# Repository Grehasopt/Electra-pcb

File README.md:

# Electra
Remote Relays Board

## Electra

> [!CAUTION]
>
> This project involves the use of 230V AC mains power and contains high-voltage components.
> Working with mains electricity can be extremely dangerous and may result in serious injury,
> death, or property damage if not handled correctly.
>
> This design is provided "as-is" and for educational purposes only.
> Only individuals with the appropriate electrical expertise and experience should attempt to
> reproduce or work with this project. You are solely responsible for ensuring that your work
> with this hardware complies with all applicable safety standards, laws, and regulations.

---

### Schematic

#### Page 1

#### Page 2

#### Page 3

#### Page 4

#### Page 5

#### Page 6

#### Page 7

#### Page 8

## License
This project is licensed under the CERN-OHL-S-2.0 (applies from the very first commit on Mar 7, 2021) with the added condition that it may not be used for commercial purposes without prior permission from the license holder.

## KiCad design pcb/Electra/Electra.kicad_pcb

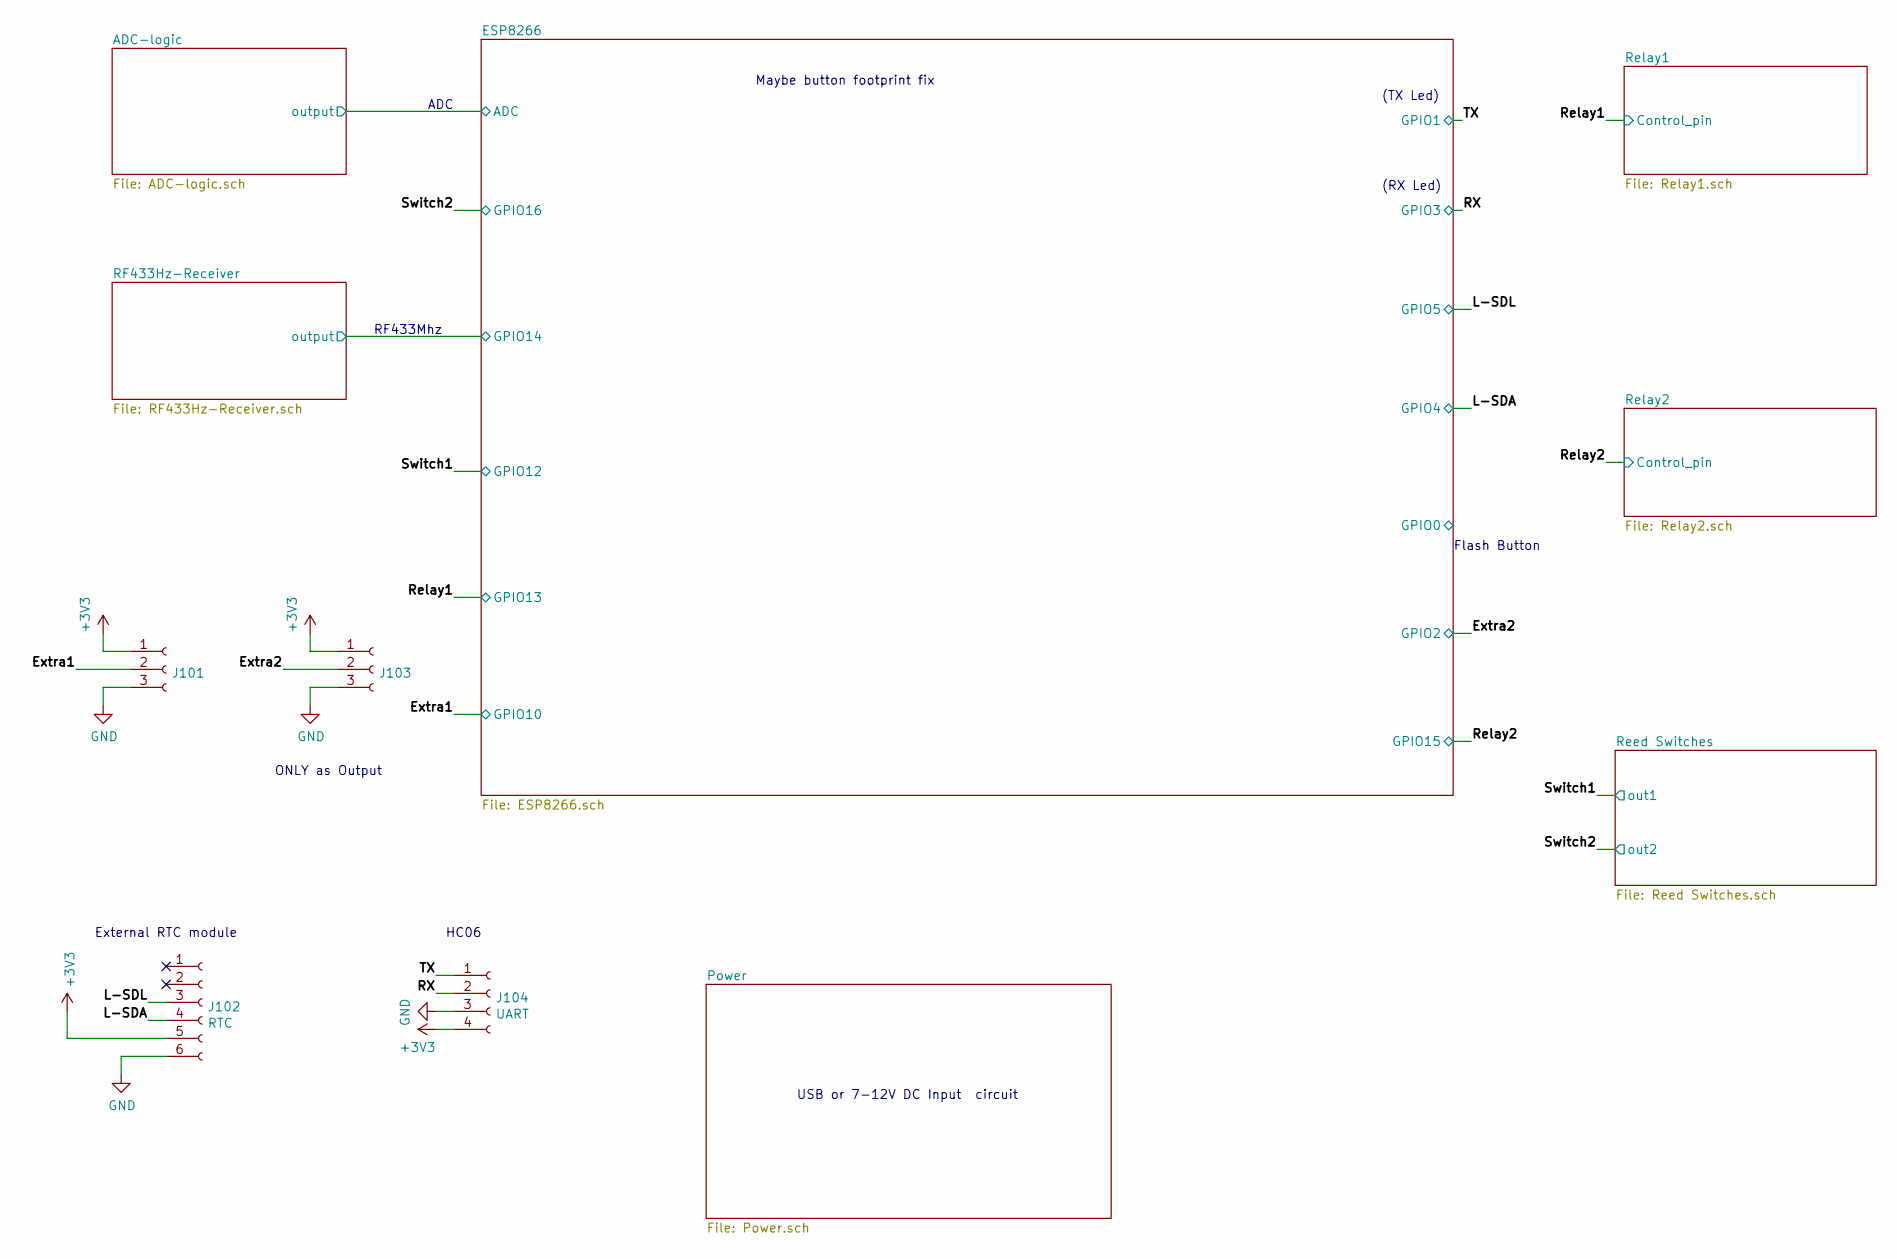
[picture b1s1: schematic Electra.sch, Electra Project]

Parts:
J101: Extra1; PinHeader_1x03_P2.54mm_Vertical
J102: RTC; PinHeader_1x06_P2.54mm_Vertical
J103: Extra2; PinHeader_1x03_P2.54mm_Vertical
J104: UART; PinHeader_1x04_P2.54mm_Vertical

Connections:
+3V3: J101.1, J102.5, J103.1, J104.4; also elsewhere on the board
/Extra1: J101.2; also elsewhere on the board
/Extra2: J103.2; also elsewhere on the board
/L-SDA: J102.4; also elsewhere on the board
/L-SDL: J102.3; also elsewhere on the board
/RX: J104.2; also elsewhere on the board
/TX: J104.1; also elsewhere on the board
GND: J101.3, J102.6, J103.3, J104.3; also elsewhere on the board

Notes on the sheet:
External RTC module
(TX Led)
(RX Led)
Flash Button
USB or 7-12V DC Input circuit
HC06
RF433Mhz
ADC
Maybe button footprint fix
ONLY as Output

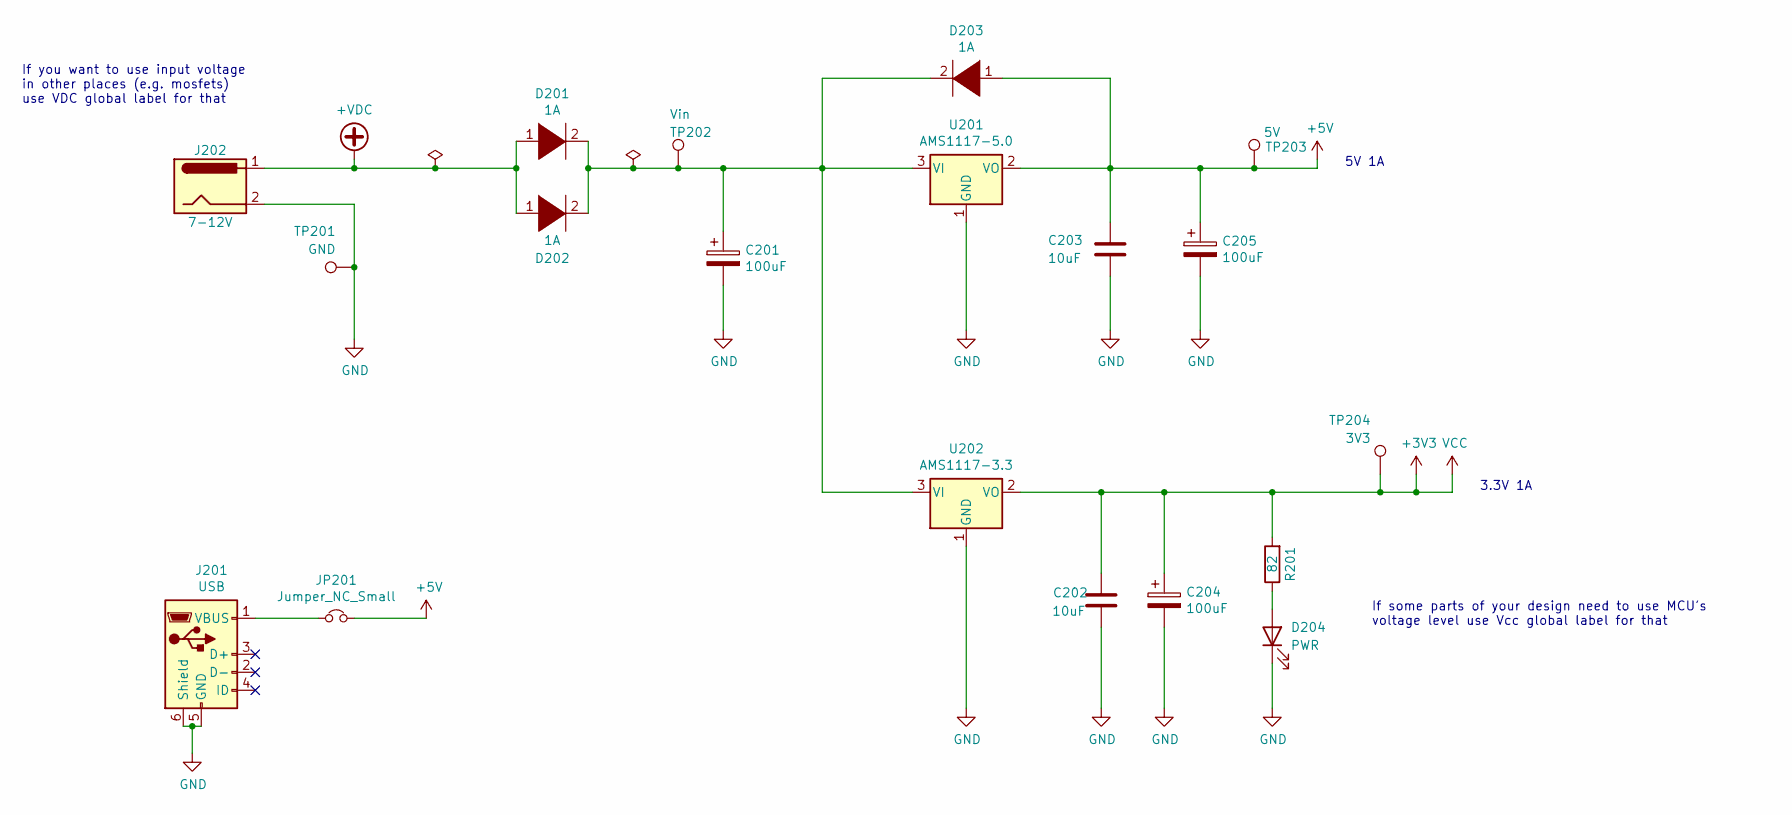
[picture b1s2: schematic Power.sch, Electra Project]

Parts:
C201, C204, C205: 100uF; CP_Elec_6.3x5.4; LCSC C97805
C202, C203: 10uF; C_0805_2012Metric_Pad1.18x1.45mm_HandSolder; LCSC C15850
D201, D202, D203: 1A; D_SMA_Handsoldering; LCSC C95872
D204: PWR; LED_0603_1608Metric_Pad1.05x0.95mm_HandSolder; LCSC C72043
J201: USB; USB_Micro-B_Molex-105017-0001; LCSC C10418
J202: 7-12V; BarrelJack_Horizontal; LCSC C16214
JP201: Jumper_NC_Small; SolderJumper-2_P1.3mm_Bridged_RoundedPad1.0x1.5mm
R201: 82; R_0603_1608Metric_Pad0.98x0.95mm_HandSolder; LCSC C23255
TP201: GND; TestPoint_Pad_D1.5mm
TP202: Vin; TestPoint_Pad_D1.5mm
TP203: 5V; TestPoint_Pad_D1.5mm
TP204: 3V3; TestPoint_Pad_D1.5mm
U201: AMS1117-5.0; SOT-223-3_TabPin2; LCSC C6187
U202: AMS1117-3.3; SOT-223-3_TabPin2; LCSC C6186

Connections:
+3V3: C202.1, C204.1, R201.2, TP204.1, U202.2 (VO); also elsewhere on the board
+5V: C203.1, C205.1, D203.1 (K), JP201.2, TP203.1, U201.2 (VO); also elsewhere on the board
+VDC: D201.1 (K), D202.1 (K), J202.1
GND: C201.2, C202.2, C203.2, C204.2, C205.2, D204.1 (K), J201.5 (GND), J201.6 (Shield), J202.2, TP201.1, U201.1 (GND), U202.1 (GND); also elsewhere on the board
unnamed: C201.1, D201.2 (A), D202.2 (A), D203.2 (A), TP202.1, U201.3 (VI), U202.3 (VI)
unnamed: D204.2 (A), R201.1
unnamed: J201.1 (VBUS), JP201.1

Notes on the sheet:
If you want to use input voltage in other places (e.g. mosfets) use VDC global label for that
If some parts of your design need to use MCU's voltage level use Vcc global label for that
5V 1A
3.3V 1A

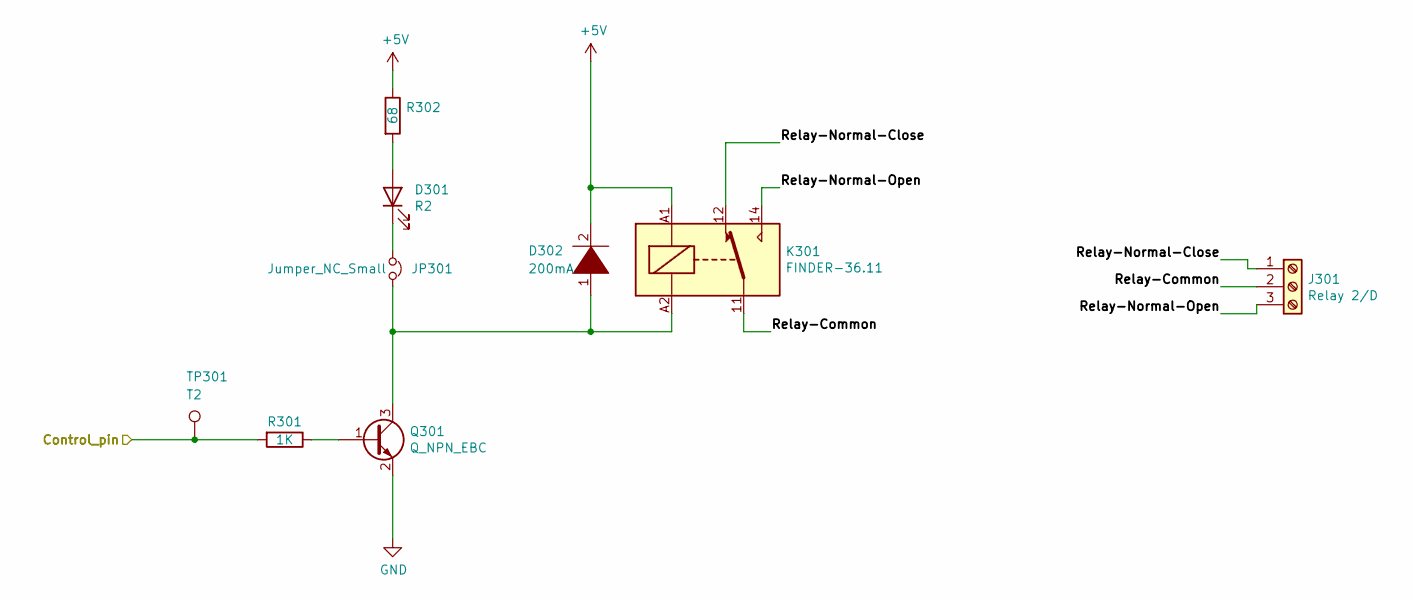
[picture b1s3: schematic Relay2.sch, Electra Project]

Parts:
D301: R2; LED_0603_1608Metric_Pad1.05x0.95mm_HandSolder; LCSC C2286
D302: 200mA; D_MiniMELF; LCSC C9808
J301: Relay 2/D; TerminalBlock_bornier-3_P5.08mm; LCSC C8425
JP301: Jumper_NC_Small; SolderJumper-2_P1.3mm_Bridged_RoundedPad1.0x1.5mm
K301: FINDER-36.11; Relay_SPDT_Finder_36.11; LCSC C399562
Q301: Q_NPN_EBC; SOT-323_SC-70; LCSC C75568
R301: 1K; R_0603_1608Metric_Pad0.98x0.95mm_HandSolder; LCSC C21190
R302: 68; R_0603_1608Metric_Pad0.98x0.95mm_HandSolder; LCSC C27592
TP301: T2; TestPoint_Pad_D1.5mm

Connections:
+5V: D302.2 (A), K301.A1, R302.1; also elsewhere on the board
/Relay2: R301.2, TP301.1; also elsewhere on the board
/Relay2/Relay-Common: J301.2, K301.11
/Relay2/Relay-Normal-Close: J301.1, K301.12
/Relay2/Relay-Normal-Open: J301.3, K301.14
GND: Q301.2 (E); also elsewhere on the board
unnamed: D301.1 (K), JP301.1
unnamed: D301.2 (A), R302.2
unnamed: D302.1 (K), JP301.2, K301.A2, Q301.3 (C)
unnamed: Q301.1 (B), R301.1

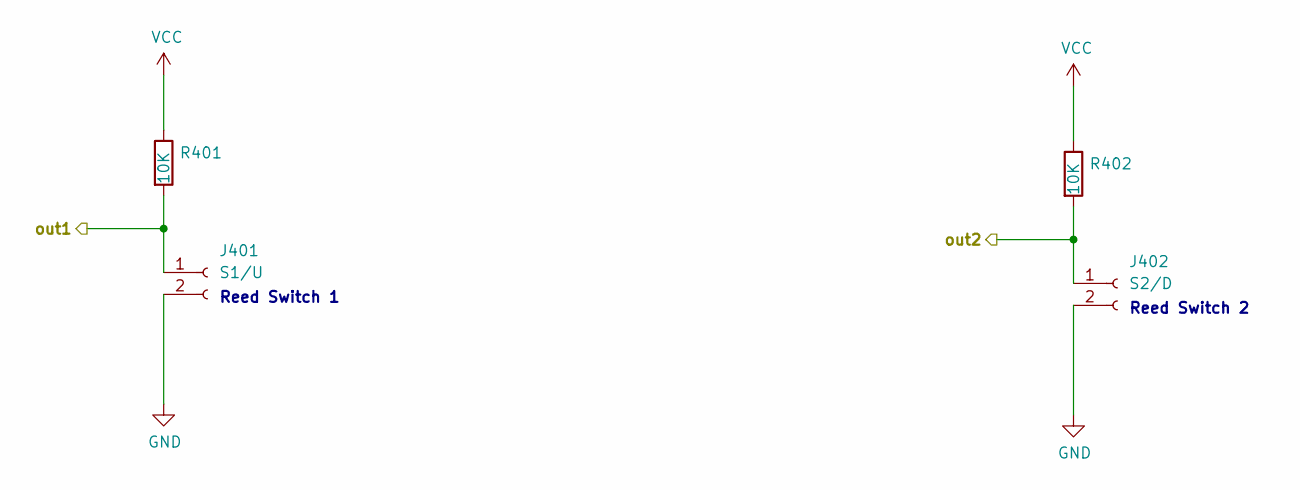
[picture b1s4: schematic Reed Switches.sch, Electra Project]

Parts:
J401: S1/U; JST_XH_B2B-XH-A_1x02_P2.50mm_Vertical
J402: S2/D; JST_XH_B2B-XH-A_1x02_P2.50mm_Vertical
R401, R402: 10K; R_0603_1608Metric_Pad0.98x0.95mm_HandSolder; LCSC C25804

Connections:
+3V3: R401.1, R402.1; also elsewhere on the board
/Switch1: J401.1, R401.2; also elsewhere on the board
/Switch2: J402.1, R402.2; also elsewhere on the board
GND: J401.2, J402.2; also elsewhere on the board

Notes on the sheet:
Reed Switch 1
Reed Switch 2

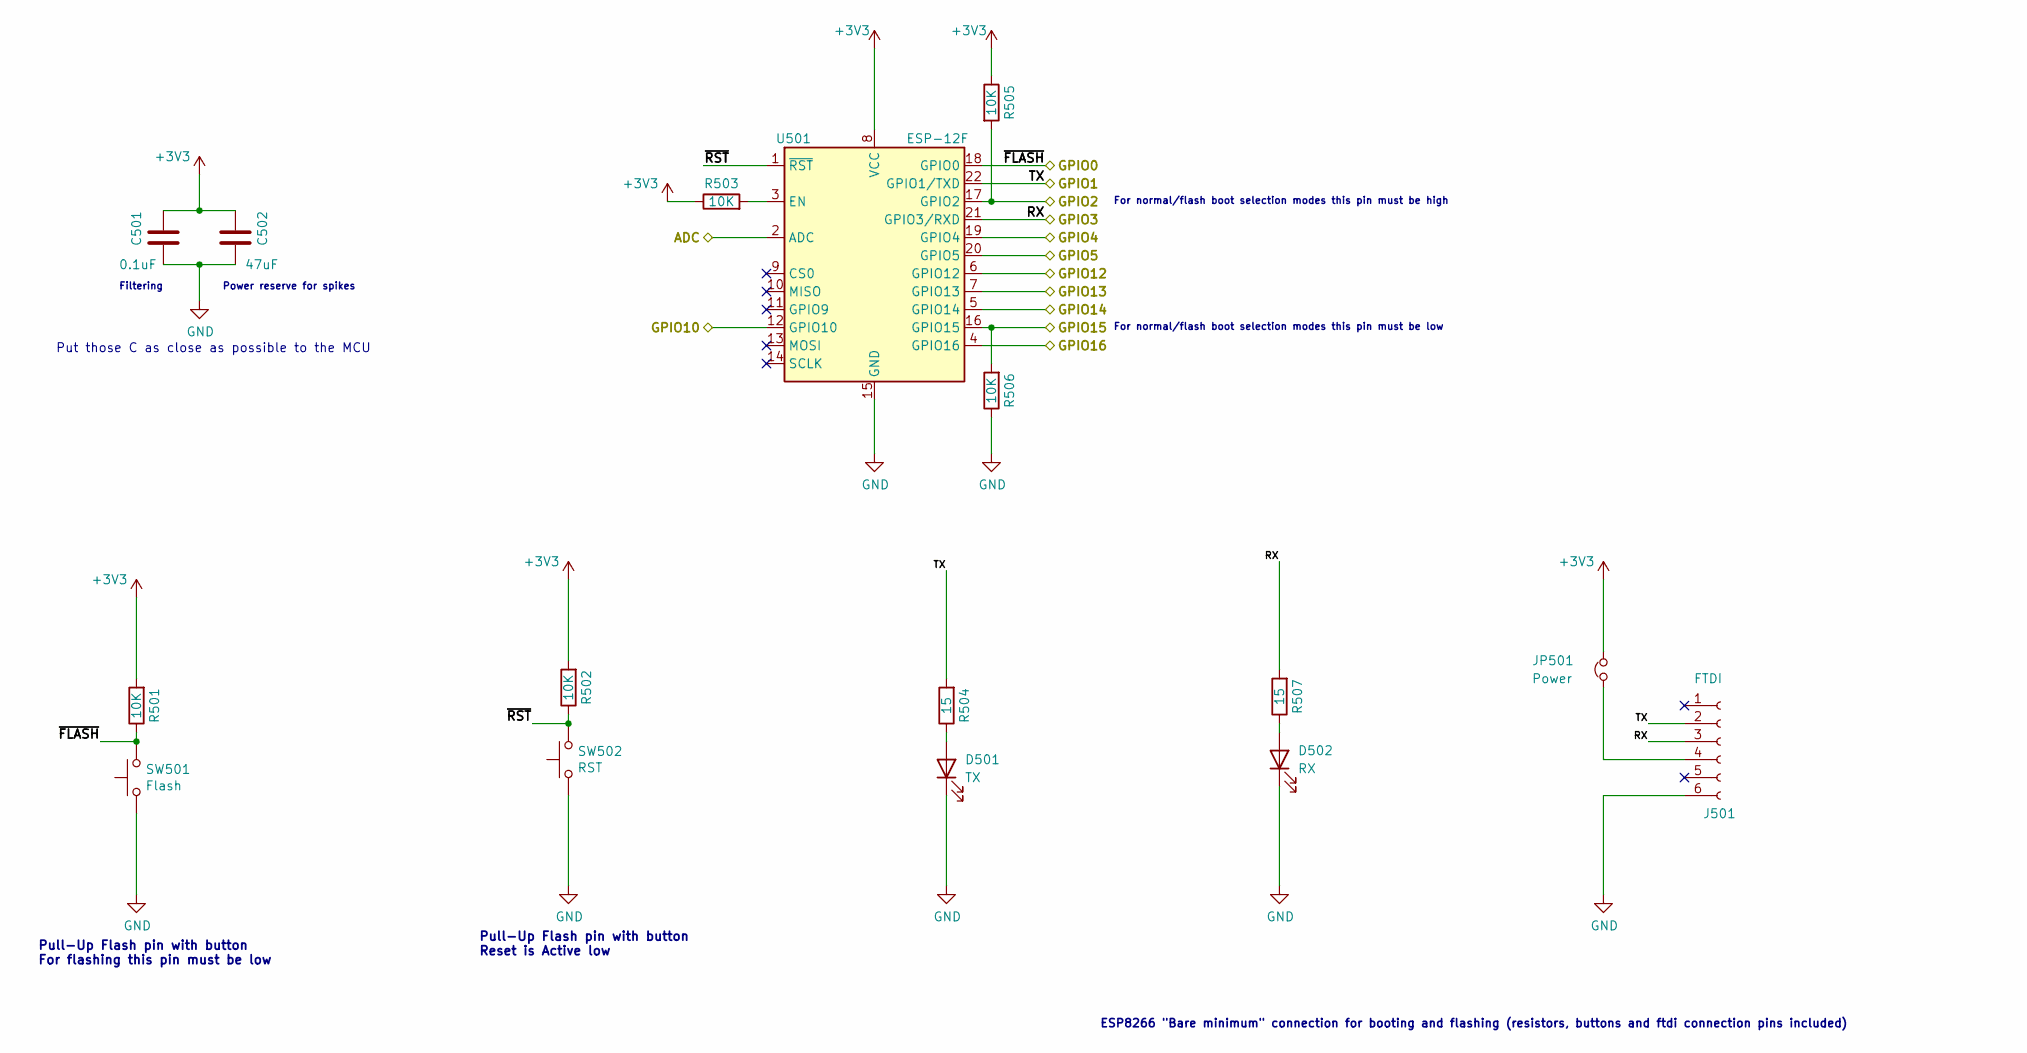
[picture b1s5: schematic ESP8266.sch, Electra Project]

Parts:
C501: 0.1uF; C_0603_1608Metric_Pad1.08x0.95mm_HandSolder; LCSC C14663
C502: 47uF; C_1206_3216Metric_Pad1.33x1.80mm_HandSolder; LCSC C96123
D501: TX; LED_0603_1608Metric_Pad1.05x0.95mm_HandSolder; LCSC C72041
D502: RX; LED_0603_1608Metric_Pad1.05x0.95mm_HandSolder; LCSC C72041
J501: FTDI; PinHeader_1x06_P2.54mm_Vertical
JP501: Power; SolderJumper-2_P1.3mm_Bridged_RoundedPad1.0x1.5mm
R501, R502, R503, R505, R506: 10K; R_0603_1608Metric_Pad0.98x0.95mm_HandSolder; LCSC C25804
R504, R507: 15; R_0805_2012Metric_Pad1.20x1.40mm_HandSolder; LCSC C17480
SW501: Flash; SW_SPST_CK_RS282G05A3; LCSC C319365
SW502: RST; SW_SPST_CK_RS282G05A3; LCSC C319365
U501: ESP-12F; ESP-12E; LCSC C82891

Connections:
+3V3: C501.1, C502.1, JP501.2, R501.2, R502.2, R503.1, R505.1, U501.8 (VCC); also elsewhere on the board
/ESP8266/ADC: U501.2 (ADC); also elsewhere on the board
/ESP8266/GPIO0: R501.1, SW501.2, U501.18 (GPIO0)
/ESP8266/GPIO14: U501.5 (GPIO14); also elsewhere on the board
/ESP8266/~RST: R502.1, SW502.2, U501.1 (~RST)
/Extra1: U501.12 (GPIO10); also elsewhere on the board
/Extra2: R505.2, U501.17 (GPIO2); also elsewhere on the board
/L-SDA: U501.19 (GPIO4); also elsewhere on the board
/L-SDL: U501.20 (GPIO5); also elsewhere on the board
/RX: J501.3, R507.2, U501.21 (GPIO3/RXD); also elsewhere on the board
/Relay1: U501.7 (GPIO13); also elsewhere on the board
/Relay2: R506.2, U501.16 (GPIO15); also elsewhere on the board
/Switch1: U501.6 (GPIO12); also elsewhere on the board
/Switch2: U501.4 (GPIO16); also elsewhere on the board
/TX: J501.2, R504.2, U501.22 (GPIO1/TXD); also elsewhere on the board
GND: C501.2, C502.2, D501.1 (K), D502.1 (K), J501.6, R506.1, SW501.1, SW502.1, U501.15 (GND); also elsewhere on the board
unnamed: D501.2 (A), R504.1
unnamed: D502.2 (A), R507.1
unnamed: J501.4, JP501.1
unnamed: R503.2, U501.3 (EN)

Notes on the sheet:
ESP8266 "Bare minimum" connection for booting and flashing (resistors, buttons and ftdi connection pins included)
For normal/flash boot selection modes this pin must be high
For normal/flash boot selection modes this pin must be low
Pull-Up Flash pin with button Reset is Active low
Filtering
Power reserve for spikes
Pull-Up Flash pin with button For flashing this pin must be low
Put those C as close as possible to the MCU

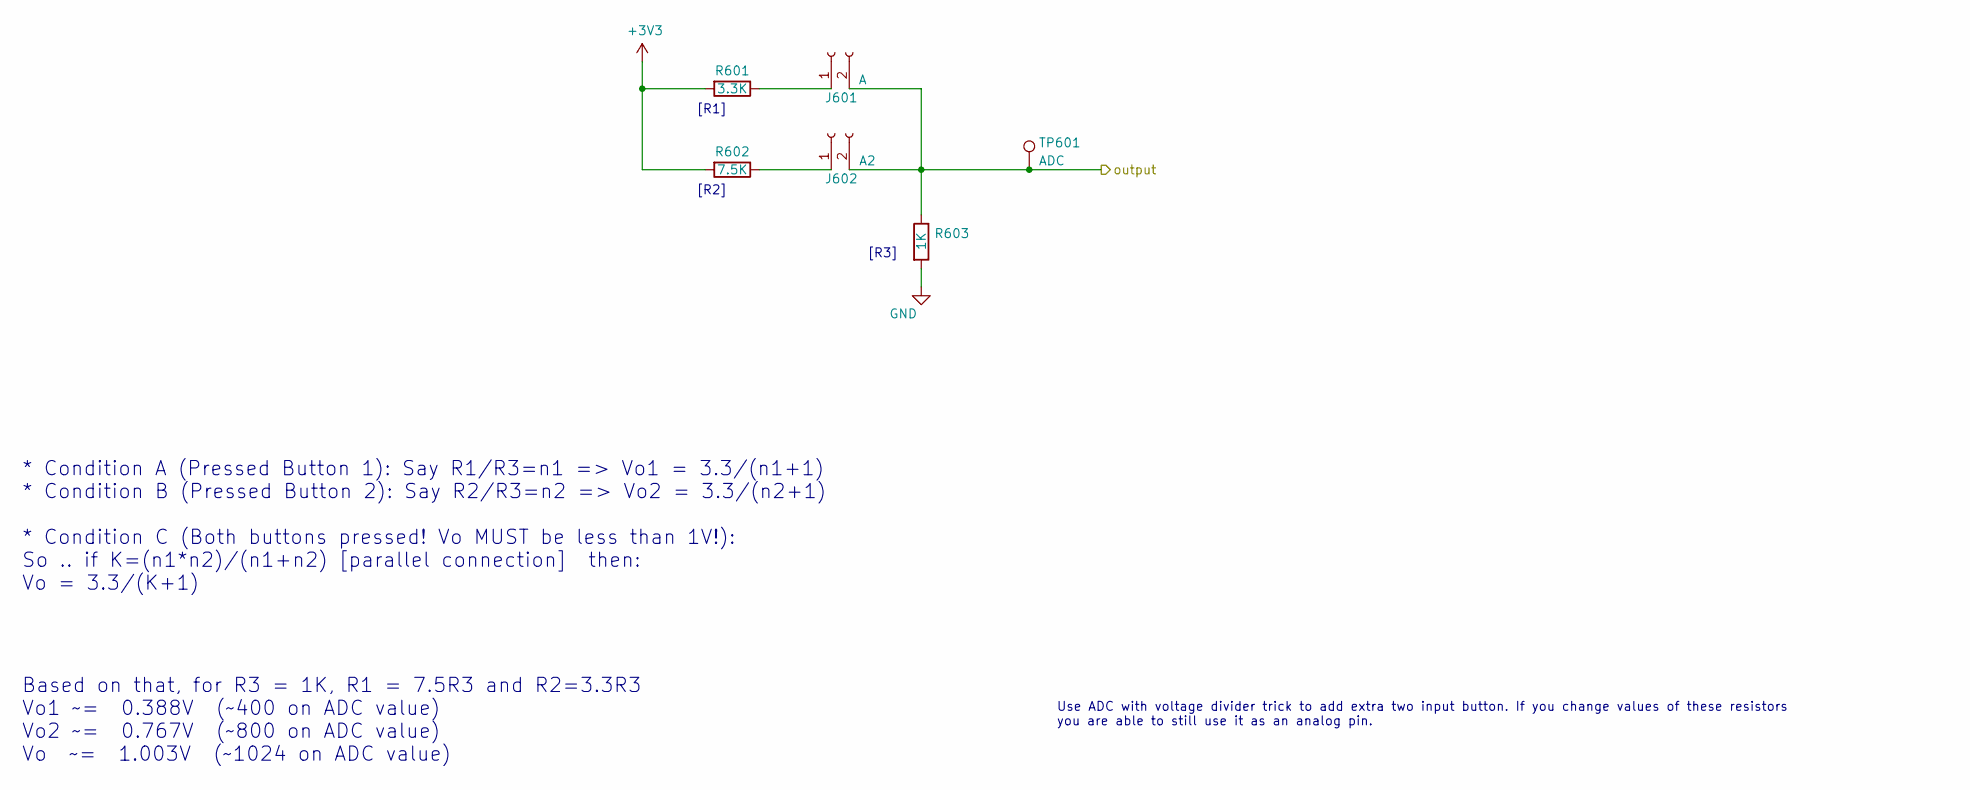
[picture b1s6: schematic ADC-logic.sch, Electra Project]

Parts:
J601: A; JST_XH_B2B-XH-A_1x02_P2.50mm_Vertical
J602: A2; JST_XH_B2B-XH-A_1x02_P2.50mm_Vertical
R601: 3.3K; R_0603_1608Metric_Pad0.98x0.95mm_HandSolder; LCSC C22978
R602: 7.5K; R_0603_1608Metric_Pad0.98x0.95mm_HandSolder; LCSC C23234
R603: 1K; R_0603_1608Metric_Pad0.98x0.95mm_HandSolder; LCSC C21190
TP601: ADC; TestPoint_Pad_D1.5mm

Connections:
+3V3: R601.2, R602.2; also elsewhere on the board
/ESP8266/ADC: J601.2, J602.2, R603.1, TP601.1; also elsewhere on the board
GND: R603.2; also elsewhere on the board
unnamed: J601.1, R601.1
unnamed: J602.1, R602.1

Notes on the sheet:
[R3]
[R1]
[R2]
* Condition A (Pressed Button 1): Say R1/R3=n1 => Vo1 = 3.3/(n1+1) * Condition B (Pressed Button 2): Say R2/R3=n2 => Vo2 = 3.3/(n2+1) * Condition C (Both buttons pressed! Vo MUST be less than 1V!): So .. if K=(n1*n2)/(n1+n2) [parallel connection] then: Vo = 3.3/(K+1)
Use ADC with voltage divider trick to add extra two input button. If you change values of these resistors you are able to still use it as an analog pin.
Based on that, for R3 = 1K, R1 = 7.5R3 and R2=3.3R3 Vo1 ~~= 0.388V (~~400 on ADC value) Vo2 ~~= 0.767V (~~800 on ADC value) Vo ~~= 1.003V (~~1024 on ADC value)

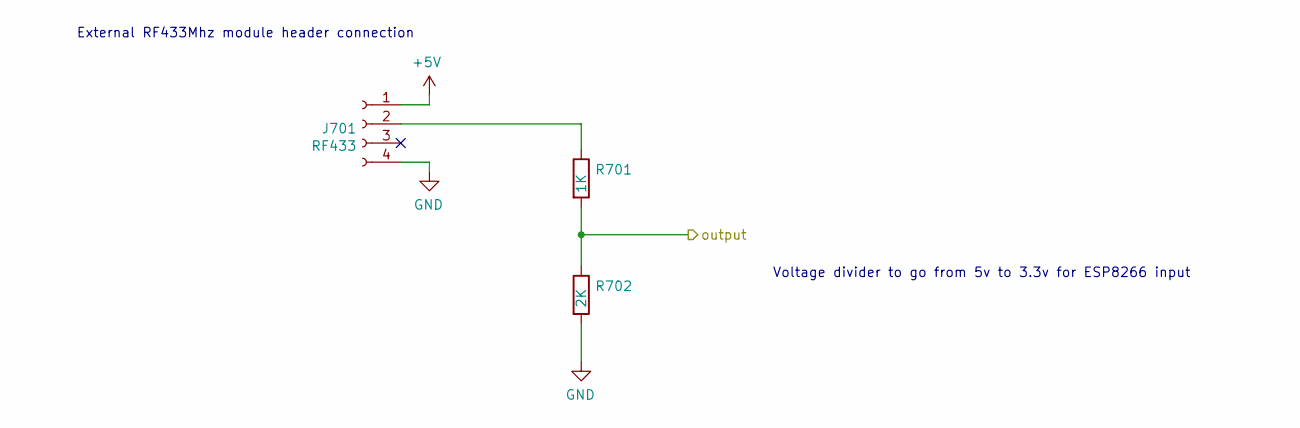
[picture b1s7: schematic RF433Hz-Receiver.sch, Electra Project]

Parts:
J701: RF433; PinHeader_1x04_P2.54mm_Vertical
R701: 1K; R_0603_1608Metric_Pad0.98x0.95mm_HandSolder; LCSC C21190
R702: 2K; R_0603_1608Metric_Pad0.98x0.95mm_HandSolder; LCSC C22975

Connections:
+5V: J701.1; also elsewhere on the board
/ESP8266/GPIO14: R701.2, R702.1; also elsewhere on the board
GND: J701.4, R702.2; also elsewhere on the board
unnamed: J701.2, R701.1

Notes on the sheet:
External RF433Mhz module header connection
Voltage divider to go from 5v to 3.3v for ESP8266 input

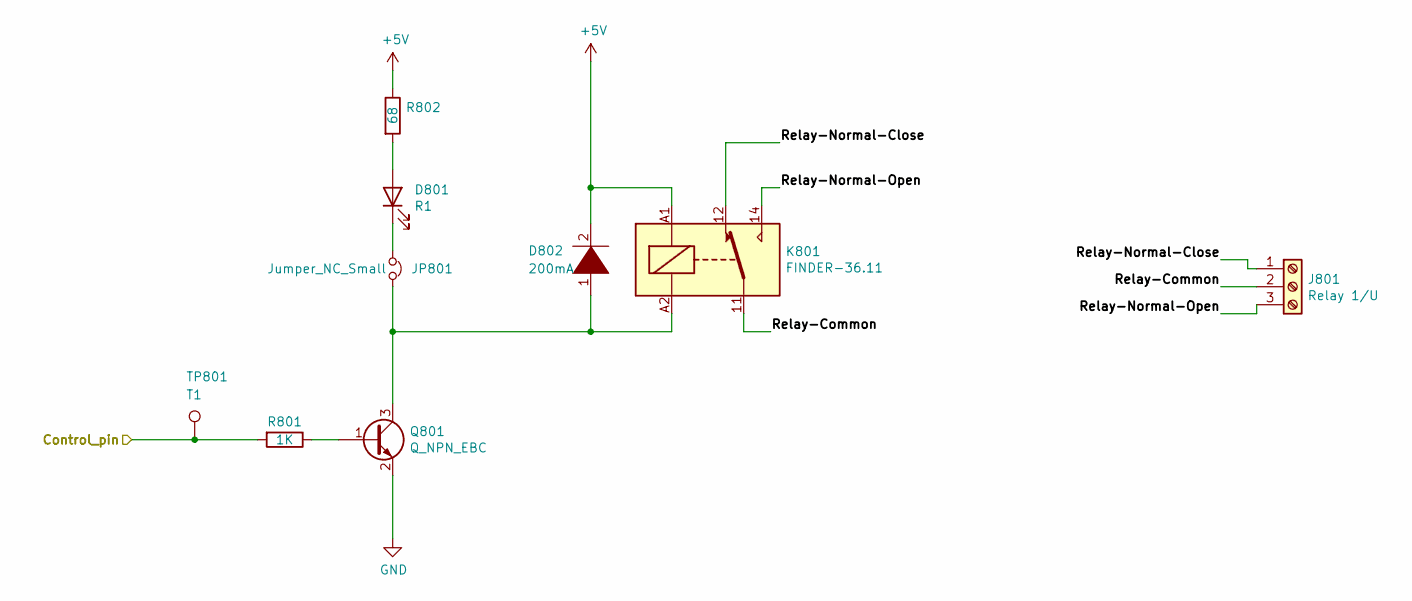
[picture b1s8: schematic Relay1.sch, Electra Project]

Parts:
D801: R1; LED_0603_1608Metric_Pad1.05x0.95mm_HandSolder; LCSC C2286
D802: 200mA; D_MiniMELF; LCSC C9808
J801: Relay 1/U; TerminalBlock_bornier-3_P5.08mm; LCSC C8425
JP801: Jumper_NC_Small; SolderJumper-2_P1.3mm_Bridged_RoundedPad1.0x1.5mm
K801: FINDER-36.11; Relay_SPDT_Finder_36.11; LCSC C399562
Q801: Q_NPN_EBC; SOT-323_SC-70; LCSC C75568
R801: 1K; R_0603_1608Metric_Pad0.98x0.95mm_HandSolder; LCSC C21190
R802: 68; R_0603_1608Metric_Pad0.98x0.95mm_HandSolder; LCSC C27592
TP801: T1; TestPoint_Pad_D1.5mm

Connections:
+5V: D802.2 (A), K801.A1, R802.1; also elsewhere on the board
/Relay1: R801.2, TP801.1; also elsewhere on the board
/Relay1/Relay-Common: J801.2, K801.11
/Relay1/Relay-Normal-Close: J801.1, K801.12
/Relay1/Relay-Normal-Open: J801.3, K801.14
GND: Q801.2 (E); also elsewhere on the board
unnamed: D801.1 (K), JP801.1
unnamed: D801.2 (A), R802.2
unnamed: D802.1 (K), JP801.2, K801.A2, Q801.3 (C)
unnamed: Q801.1 (B), R801.1

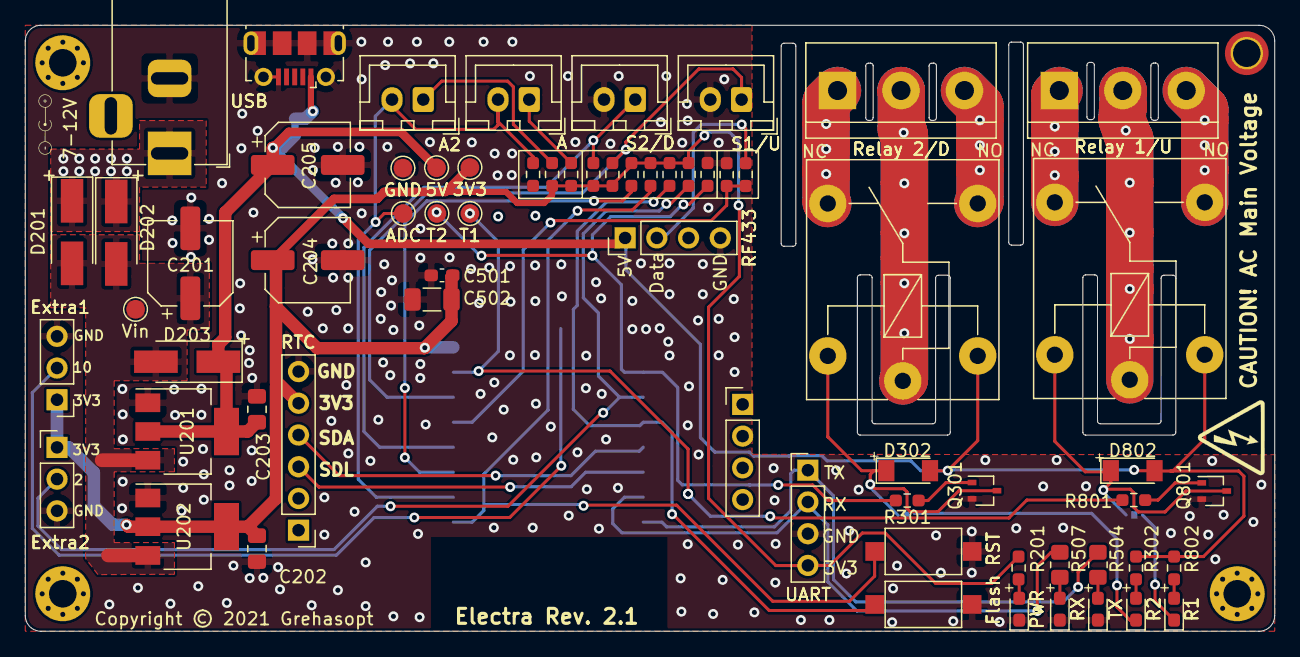
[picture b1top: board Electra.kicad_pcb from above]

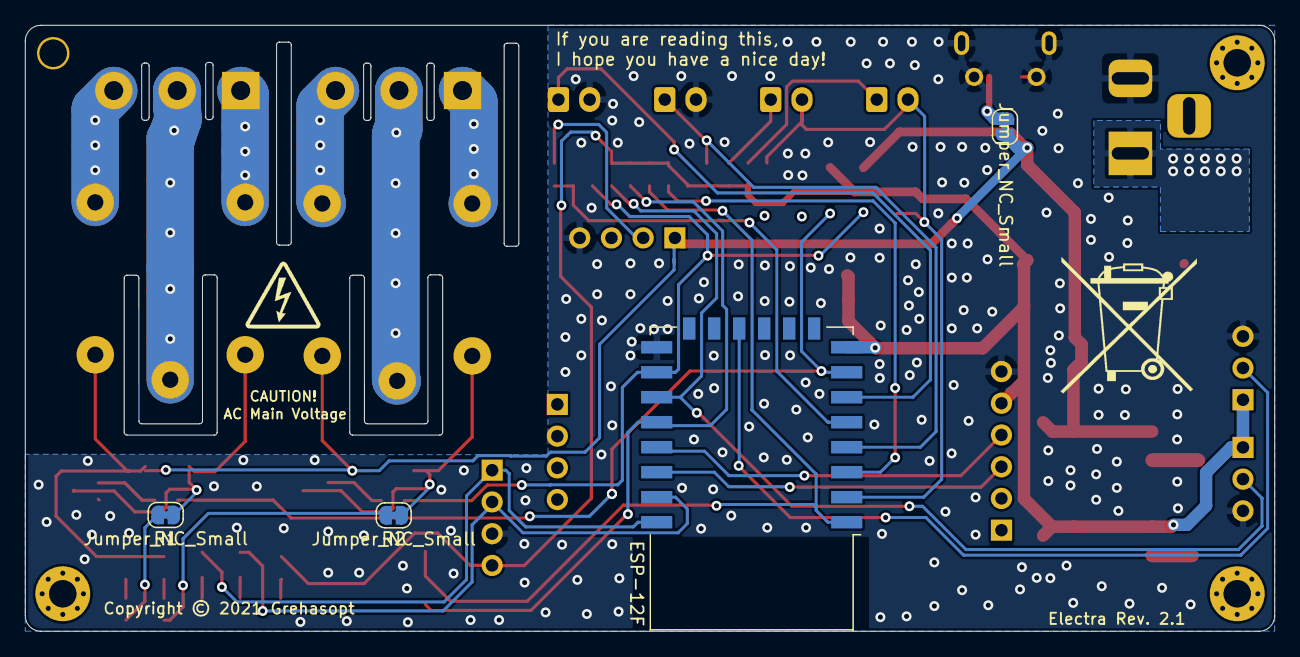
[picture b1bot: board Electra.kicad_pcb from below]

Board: 2 copper layers, 100.0 x 48.5 mm, 68 parts (4 on the bottom side), 41 nets.

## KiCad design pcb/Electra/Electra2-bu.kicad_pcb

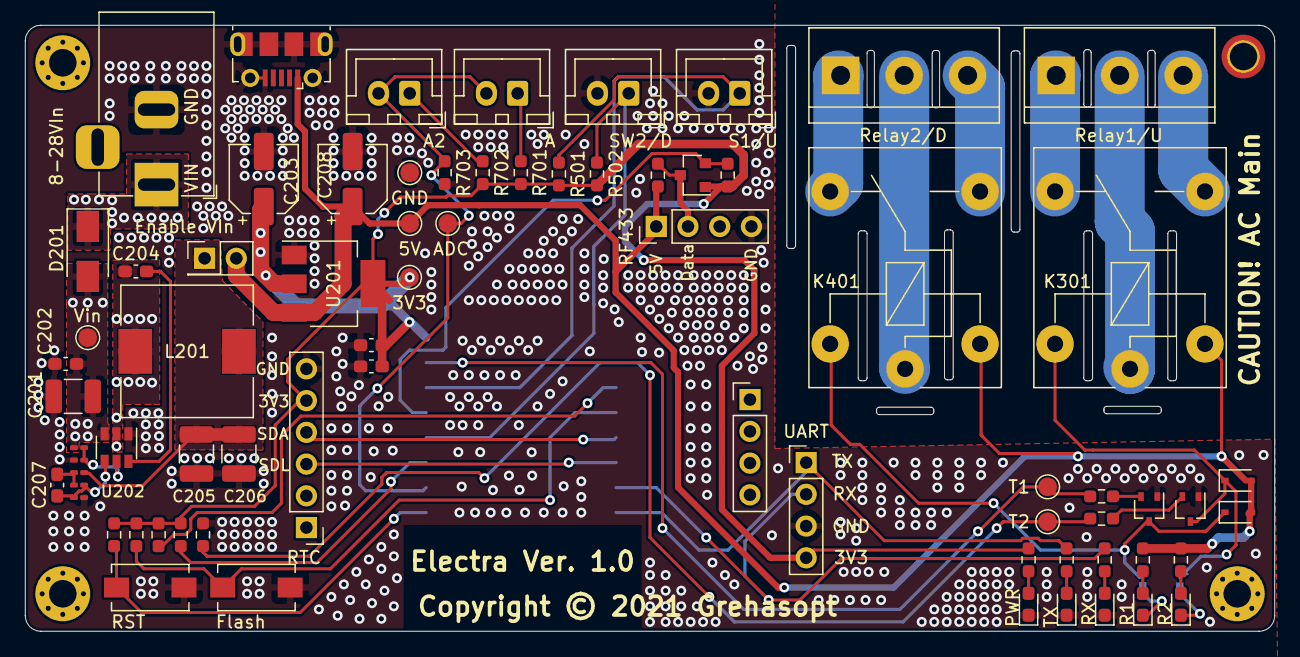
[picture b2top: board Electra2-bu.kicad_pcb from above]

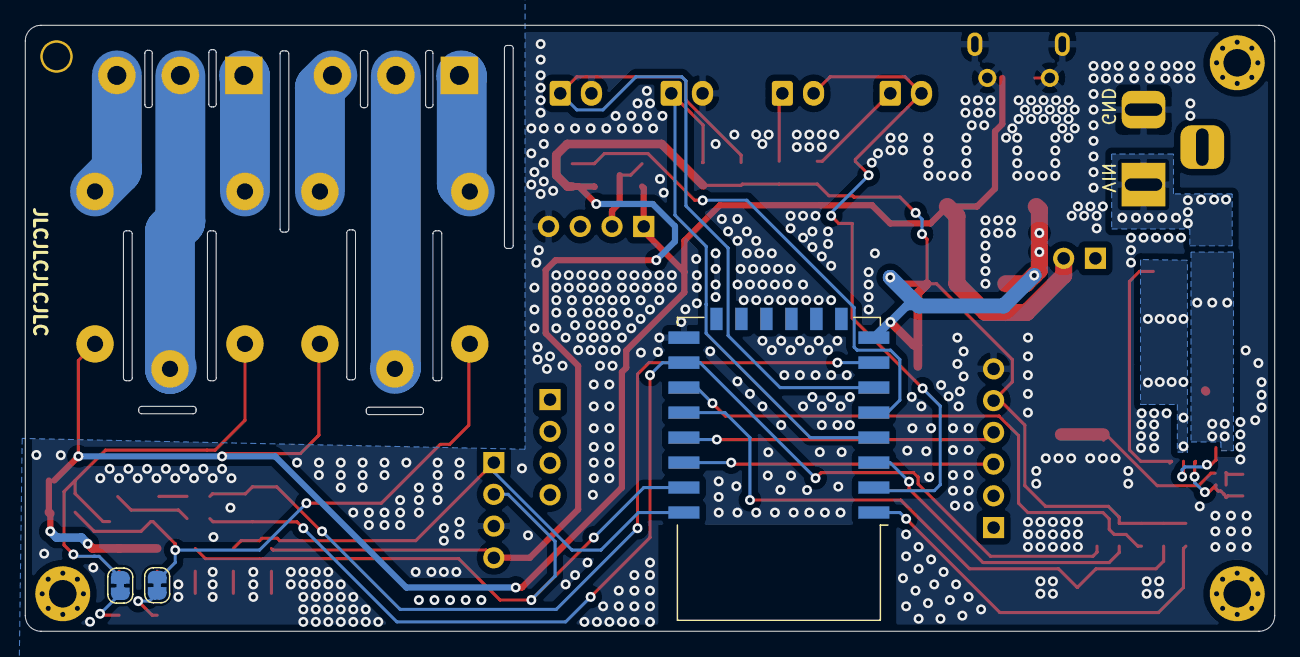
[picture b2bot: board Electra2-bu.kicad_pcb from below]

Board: 2 copper layers, 100.0 x 48.5 mm, 74 parts (3 on the bottom side), 45 nets.

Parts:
C201: 10uF; C_1210_3225Metric_Pad1.33x2.70mm_HandSolder
C202, C204, C601: 0.1uF; C_0603_1608Metric_Pad1.08x0.95mm_HandSolder
C203, C208: 100uF; CP_Elec_5x5.4
C205, C206: 22uF; C_1210_3225Metric_Pad1.33x2.70mm_HandSolder
C207: 75pF; C_0603_1608Metric_Pad1.08x0.95mm_HandSolder
C602: 47uF; C_0603_1608Metric_Pad1.08x0.95mm_HandSolder
D201: DIODE; D_SMA
D202: PWR; LED_0603_1608Metric_Pad1.05x0.95mm_HandSolder
D301: R2; LED_0603_1608Metric_Pad1.05x0.95mm_HandSolder
D302, D402: DIODE; D_SOD-323
D401: R1; LED_0603_1608Metric_Pad1.05x0.95mm_HandSolder
D601: TX; LED_0603_1608Metric_Pad1.05x0.95mm_HandSolder
D602: RX; LED_0603_1608Metric_Pad1.05x0.95mm_HandSolder
J101: RTC; PinHeader_1x06_P2.54mm_Vertical
J102: UART; PinHeader_1x04_P2.54mm_Vertical
J201: 8-28VIn; BarrelJack_Horizontal
J202: USB_B_Micro; USB_Micro-B_Molex-105017-0001
J203: Enable VIn; PinHeader_2x01_P2.54mm_Vertical
J301: Relay1/U; TerminalBlock_bornier-3_P5.08mm
J401: Relay2/D; TerminalBlock_bornier-3_P5.08mm
J501: S1/U; JST_XH_B2B-XH-A_1x02_P2.50mm_Vertical
J502: SW2/D; JST_XH_B2B-XH-A_1x02_P2.50mm_Vertical
J701: A; JST_XH_B2B-XH-A_1x02_P2.50mm_Vertical
J702: A2; JST_XH_B2B-XH-A_1x02_P2.50mm_Vertical
J801: RF433; PinHeader_1x04_P2.54mm_Vertical
JP301, JP401: Jumper_NC_Small; SolderJumper-2_P1.3mm_Bridged_RoundedPad1.0x1.5mm
K301, K401: FINDER-36.11; Relay_SPDT_Finder_36.11
L201: 15uH; L_10.4x10.4_H4.8
Q301, Q401: Q_NPN_EBC; SOT-323_SC-70
Q801: BSS138; SOT-23
R201: 511K; R_0201_0603Metric_Pad0.64x0.40mm_HandSolder
R202: 105K; R_0201_0603Metric_Pad0.64x0.40mm_HandSolder
R203, R604, R607: 80; R_0603_1608Metric_Pad0.98x0.95mm_HandSolder
R204: 49.9; R_0201_0603Metric_Pad0.64x0.40mm_HandSolder
R205: 100K; R_0201_0603Metric_Pad0.64x0.40mm_HandSolder
R206: 13.3K; R_0201_0603Metric_Pad0.64x0.40mm_HandSolder
R301, R401, R703: 1K; R_0603_1608Metric_Pad0.98x0.95mm_HandSolder
R302, R402: 150; R_0603_1608Metric_Pad0.98x0.95mm_HandSolder
R501, R502, R601, R602, R603, R605, R606, R801, R802: 10K; R_0603_1608Metric_Pad0.98x0.95mm_HandSolder
R701: 3.57K; R_0603_1608Metric_Pad0.98x0.95mm_HandSolder
R702: 7.5K; R_0603_1608Metric_Pad0.98x0.95mm_HandSolder
SW601: Flash; SW_SPST_EVQPE1
SW602: RST; SW_SPST_EVQPE1
TP201: GND; TestPoint_Pad_D1.5mm
TP202: Vin; TestPoint_Pad_D1.5mm
TP203: 3V3; TestPoint_Pad_D1.5mm
TP204: 5V; TestPoint_Pad_D1.5mm
TP301: T2; TestPoint_Pad_D1.5mm
TP401: T1; TestPoint_Pad_D1.5mm
TP701: ADC; TestPoint_Pad_D1.5mm
U201: AMS1117-3.3; SOT-223-3_TabPin2
U202: TPS54202DDCR; SOT-23-6
U601: ESP-12F; ESP-12E

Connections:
+3V3: C203.1, C601.1, C602.1, J101.5, J102.4, Q801.1, R203.2, R501.1, R502.1, R601.2, R602.2, R603.1, R605.1, R701.2, R702.2, R801.1, TP203.1, U201.2, U601.8
+5V: C208.1, D302.2, D402.2, J202.1, J203.2, J801.1, K301.A1, K401.A1, R302.1, R402.1, R802.1, TP204.1, U201.3
+VDC: D201.1, J201.1
/ESP8266/ADC: J701.2, J702.2, R703.1, TP701.1, U601.2
/ESP8266/GPIO0: R601.1, SW601.2, U601.18
/ESP8266/GPIO2: R605.2, U601.17
/ESP8266/GPIO14: Q801.2, R801.2, U601.5
/ESP8266/~RST: R602.1, SW602.2, U601.1
/L-SDA: J101.4, U601.19
/L-SDL: J101.3, U601.20
/RX: J102.2, R607.2, U601.21
/Relay1: R401.2, TP401.1, U601.7
/Relay1/Relay-Common: J401.2, K401.11
/Relay1/Relay-Normal-Close: J401.1, K401.12
/Relay1/Relay-Normal-Open: J401.3, K401.14
/Relay2: R301.2, R606.2, TP301.1, U601.16
/Relay2/Relay-Common: J301.2, K301.11
/Relay2/Relay-Normal-Close: J301.1, K301.12
/Relay2/Relay-Normal-Open: J301.3, K301.14
/Switch1: J501.1, R501.2, U601.6
/Switch2: J502.1, R502.2, U601.4
/TX: J102.1, R604.2, U601.22
GND: C201.2, C202.2, C203.2, C205.1, C206.1, C208.2, C601.2, C602.2, D202.1, D601.1, D602.1, J101.6, J102.3, J201.2, J202.5, J202.6, J501.2, J502.2, J801.4, Q301.1, Q401.1, R202.2, R206.2, R606.1, R703.2, SW601.1, SW602.1, TP201.1, U201.1, U202.1, U601.15
unnamed: C201.1, C202.1, D201.2, R201.1, TP202.1, U202.3
unnamed: C204.1, L201.1, U202.2
unnamed: C204.2, U202.6
unnamed: C205.2, C206.2, J203.1, L201.2, R204.1
unnamed: C207.1, R205.2, R206.1, U202.4
unnamed: C207.2, R204.2, R205.1
unnamed: D202.2, R203.1
unnamed: D301.1, JP301.1
unnamed: D301.2, R302.2
unnamed: D302.1, JP301.2, K301.A2, Q301.3
unnamed: D401.1, JP401.1
unnamed: D401.2, R402.2
unnamed: D402.1, JP401.2, K401.A2, Q401.3
unnamed: D601.2, R604.1
unnamed: D602.2, R607.1
unnamed: J701.1, R701.1
unnamed: J702.1, R702.1
unnamed: J801.2, Q801.3, R802.2
unnamed: Q301.2, R301.1
unnamed: Q401.2, R401.1
unnamed: R201.2, R202.1, U202.5
unnamed: R603.2, U601.3

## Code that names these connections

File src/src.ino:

#include <Arduino.h>
#include <RCSwitch.h>
#include "DS3231.h"

RCSwitch mySwitch = RCSwitch();
DS3231 ds;

int Relay1 = 15;
int Relay2 = 13;

int Switch1 = 16;
int Switch2 = 12;

int rfPin = 14;

long timer;

int led1 = 1;
int led2 = 3;

void setup(){
//    Serial.begin(115/200);
    Serial.println("\n--------------------------------------------------\nHello");

    pinMode(Relay1, OUTPUT);
    digitalWrite(Relay1, LOW);

    pinMode(Relay2, OUTPUT);
    digitalWrite(Relay2, LOW);

    pinMode(Switch1, INPUT);
    pinMode(Switch2, INPUT);

    mySwitch.enableReceive(rfPin); 
    ds.setupDateTimeBasedCompile();
    timer = millis();

    pinMode(led1,OUTPUT);
    pinMode(led2,OUTPUT);
    digitalWrite(led1, LOW);
    digitalWrite(led2, LOW);
}


void loop(){
    
    //1
    if(!digitalRead(Switch1)){
        digitalWrite(Relay1, HIGH);
        digitalWrite(led1, HIGH);
    }
    else{
        digitalWrite(Relay1, LOW);
        digitalWrite(led1, LOW);
    }

    //2
    if(!digitalRead(Switch2)){
        digitalWrite(Relay2, HIGH);
        digitalWrite(led2, HIGH);
    }
    else{
        digitalWrite(Relay2, LOW);
        digitalWrite(led2, LOW);
    }

    if (mySwitch.available()) {
        Serial.print("Received ");
        Serial.print( mySwitch.getReceivedValue() );
        Serial.print(" / ");
        Serial.print( mySwitch.getReceivedBitlength() );
        Serial.print("bit ");
        Serial.print("Protocol: ");
        Serial.println( mySwitch.getReceivedProtocol() );
    //    Serial.print((char)mySwitch.getReceivedValue());
        mySwitch.resetAvailable();
    }
    
    if(millis() -  timer >= 3000){
        ds.diagnosticPrints();
        timer = millis();
    }
}

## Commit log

2021-03-21 Basic schematic added v1
2021-03-24 PCB Ver 1 completed (TODO: Check)
2021-03-25 PCB completed (added silkscreen more)
2021-03-27 Pcb completed with 3D model
2021-03-28 Panel added, gerbs added
2021-03-28 Release 1.0 | Rev 1.0 (TPS54202DDCR out of stock) use different buck converter
2021-04-01 Rev 2 completed, todo check all and remove not needed filed
2021-04-02 IMPORTANT! REV 2 completed! Send to fabrication
2021-04-07 Added gitignore
2021-04-07 Git ignore remove committed files
2021-05-04 Clean some vias and clean up files
2021-05-04 Minor fixes on schematic and pcb fix bjt netlist + ac main voltage to both sides (Rev 2.1)
2024-11-07 Update LICENSE

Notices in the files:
pcb/Electra/Electra.kicad_pcb:
Copyright © 2021 Grehasopt
